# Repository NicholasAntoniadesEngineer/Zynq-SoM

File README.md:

# schgen

Generates the Zynq carrier and devkit boards from their C++ circuit definitions:
checked schematics, a placed board, design rules, manufacturing files and renders.
Routing is not done yet.

## Build

```sh
./build
```

Compiles the tool and runs the test suite (about 17 minutes). `./build --no-tests`
only compiles. Needs CMake, Ninja, ccache, a C++17 compiler, KiCad 10 and the
libraries listed in [native/ci/README.md](native/ci/README.md).

## Run

```sh
./run
```

Builds every board listed in `schgen.json` into `out/<board>/`. To build one board,
name it: `./run carrier`. A run ends with `BOARD: PASS` or `BOARD: FAIL`.

## Settings

Every setting lives in [`schgen.json`](schgen.json). Edit the file and run again;
nothing needs recompiling. A misspelt or unknown key stops the run with an error.

| Key | Default | Meaning |
|---|---|---|
| `boards` | `["carrier", "devkit_mini"]` | Boards to build, each a folder in this repository |
| `output` | `"out"` | Folder that receives one sub-folder per board |
| `squeeze` | `true` | Compact the placed board to the smallest outline that passes every rule |
| `arrange` | `true` | Before squeezing, move clusters of parts off sides of the module so those sides can close up; needs `squeeze` |
| `construct` | `false` | Before repair and squeezing, take every part that belongs to an owner off the board and seat it again by the layout rules; needs `squeeze` |
| `plan` | `true` | After the start is repaired, lift every group of tied parts that is free to move and seat it again, sheet by sheet, nearest the pins it connects to, with power and fast nets counted more heavily; then offer each group a nearer place. Every layout rule is checked on each seat. `reports/board_plan.txt` lists the wiring between sheets and how compact each sheet is; needs `squeeze` |
| `renders` | `true` | Produce the 3D and per-sheet images |
| `labels` | `false` | After the layout is final, seat each part's reference label beside it on its own face and draw the function labels. Parts never move for a label; one with no free seat is hidden and listed in `reports/label_seats.txt` |
| `timing` | `true` | Print how long each stage took |
| `plane_net` | `"GND"` | Net of the reference planes |
| `audit_projections` | `2` | Source audits run side by side (1 or 2) |
| `stackup` | `JLC06161H-3313` per board | Layer build-up, by name from the catalogue below |
| `density` | `10` per board | Layout density from 1 (sparse) to 10 (dense). 10 lets courtyards touch; each level below it adds 0.25 mm between courtyards on the same face, so 5 adds 1.25 mm and 1 adds 2.25 mm. No other rule is relaxed. Parts that a rule keeps together (a decoupling capacitor and its pin, a regulator and its loop, parts on one thermal area) keep no added gap between them; the gap opens between such clusters and around parts tied to nothing. One subsystem can state its own level with `"density": N` on its row under `sheets` in the board's `board.json`. Needs `squeeze` below 10. `reports/layout_density.txt` states the levels, the gaps, the table with its sources and every pair another rule limited |
| `overmold_parts` | `["HDMI-019S"]` on the carrier | Connectors whose cable overmould needs side clearance |
| `fabrication` | per board: `fabricator`, `copper`, `finish`, `assembly_service`, `build_count` | Which fabricator profile (`fabricators/<name>.json`) judges the board and orders it; see [docs/FABRICATION.md](docs/FABRICATION.md) |
| `study` | four builds, one per layer count | Optional: `stackups` lists the builds `study layers` compares |

## Layer build-ups

[`native/stackups.json`](native/stackups.json) lists the fabricator's standard
4, 6, 8 and 10-layer builds. To try another, put its name under `stackup` and run
again. The placed layout carries over between any two builds that have a ground
plane under both faces. To add a build, add an entry to that file.

To compare builds side by side, run `native/bin/schgen study layers` (optionally
`devkit_mini --stackups JLC06161H-3313,JLC08161H-3313`). Each build goes to
`out/study/<build>/<board>/` and the comparison to `out/study/layers_<board>.txt`
and `.json`. A build that fails a gate is recorded in its column; the rest still run.

## Where things are

| Folder | Holds |
|---|---|
| `carrier/`, `devkit_mini/` | Each board's design data and generated outputs |
| `subsystems/`, `parts/` | Shared circuit blocks and part data |
| `native/` | The tool's source and tests |
| `docs/` | Background; start with [docs/OVERVIEW.md](docs/OVERVIEW.md) |

`native/bin/schgen tools` lists the individual commands used for diagnosis.

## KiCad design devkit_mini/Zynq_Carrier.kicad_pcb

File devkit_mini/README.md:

<!-- schgen:gallery -->
<!-- GENERATED by `schgen gallery` — edits between these markers are overwritten -->
## Generated 3D board views

The placed board rendered from 8 angles by `schgen board` (kicad-cli, the real component 3D models) — regenerated and committed every build, just like the sheets below.

|   |   |   |   |
|---|---|---|---|
| <br>**Perspective (front)** | <br>**Perspective (rear)** | <br>**Top** | <br>**Bottom** |
| <br>**Front edge** | <br>**Back edge** | <br>**Left edge** | <br>**Right edge** |

## Ratsnest views

Placed-board airwires, regenerated by `schgen board`: blue/orange = the subsystem's parts (top/bottom side), steel = SoM, green = intra-subsystem, red = to the SoM. `wired` = in `placement.wired_sheets`.

|   |   |
|---|---|
| <br>**Board (top)** | <br>**Board (bottom)** |
| <br>**SoM region** |   |

|   |   |   |   |
|---|---|---|---|
| <br>**debug_boot** | <br>**mechanical** | <br>**pd_input** | <br>**power** |
| <br>**power_mon** | <br>**power_som** | <br>**uart_bridge** | <br>**usb_uart_connector** |

## Generated schematics

Block diagram and all 12 devkit_mini sheets, regenerated by `schgen board` —
every PNG below passed the netlist, ERC and visual gates.

|   |   |   |
|---|---|---|
| <br>**debug_boot** | <br>**mechanical** | <br>**pd_input** |
| <br>**power** | <br>**power_mon** | <br>**power_som** |
| <br>**som_decoupling** | <br>**som_j1** | <br>**som_j2** |
| <br>**som_j3** | <br>**uart_bridge** | <br>**usb_uart_connector** |

| sheet | description |
|---|---|
| [debug_boot](renders/debug_boot.png) | JTAG + SWD headers, boot-request DIP, reset |
| [mechanical](renders/mechanical.png) | Mechanical: M3 mounts + chassis-GND bond (fiducials are PCB-only, emitted by the placer) |
| [pd_input](renders/pd_input.png) | Power inlet: USB-C PD 20V/3A + TPS26631 eFuse |
| [power](renders/power.png) | Power: +VIN->+5V->+3V3 bucks + +1V8 LDO, PG LEDs |
| [power_mon](renders/power_mon.png) | Rail telemetry: 2x INA3221 + shunts (I2C 0x40/41) |
| [power_som](renders/power_som.png) | Power: +VIN -> +5V_SOM always-on buck |
| [som_decoupling](renders/som_decoupling.png) | SoM power-entry decoupling under the DF40 mezzanine |
| [som_j1](renders/som_j1.png) | SoM J1: power / USB / STM32 / JTAG / SDIO / ETH MDI |
| [som_j2](renders/som_j2.png) | SoM J2: FPGA bank 13/33 IO + VCCO rails |
| [som_j3](renders/som_j3.png) | SoM J3: FPGA bank 33/34/35 IO + VCCO rails |
| [uart_bridge](renders/uart_bridge.png) | UART bridge: CP2102N USB-UART |
| [usb_uart_connector](renders/usb_uart_connector.png) | USB-C UFP console port -> CP2102N |
<!-- /schgen:gallery -->

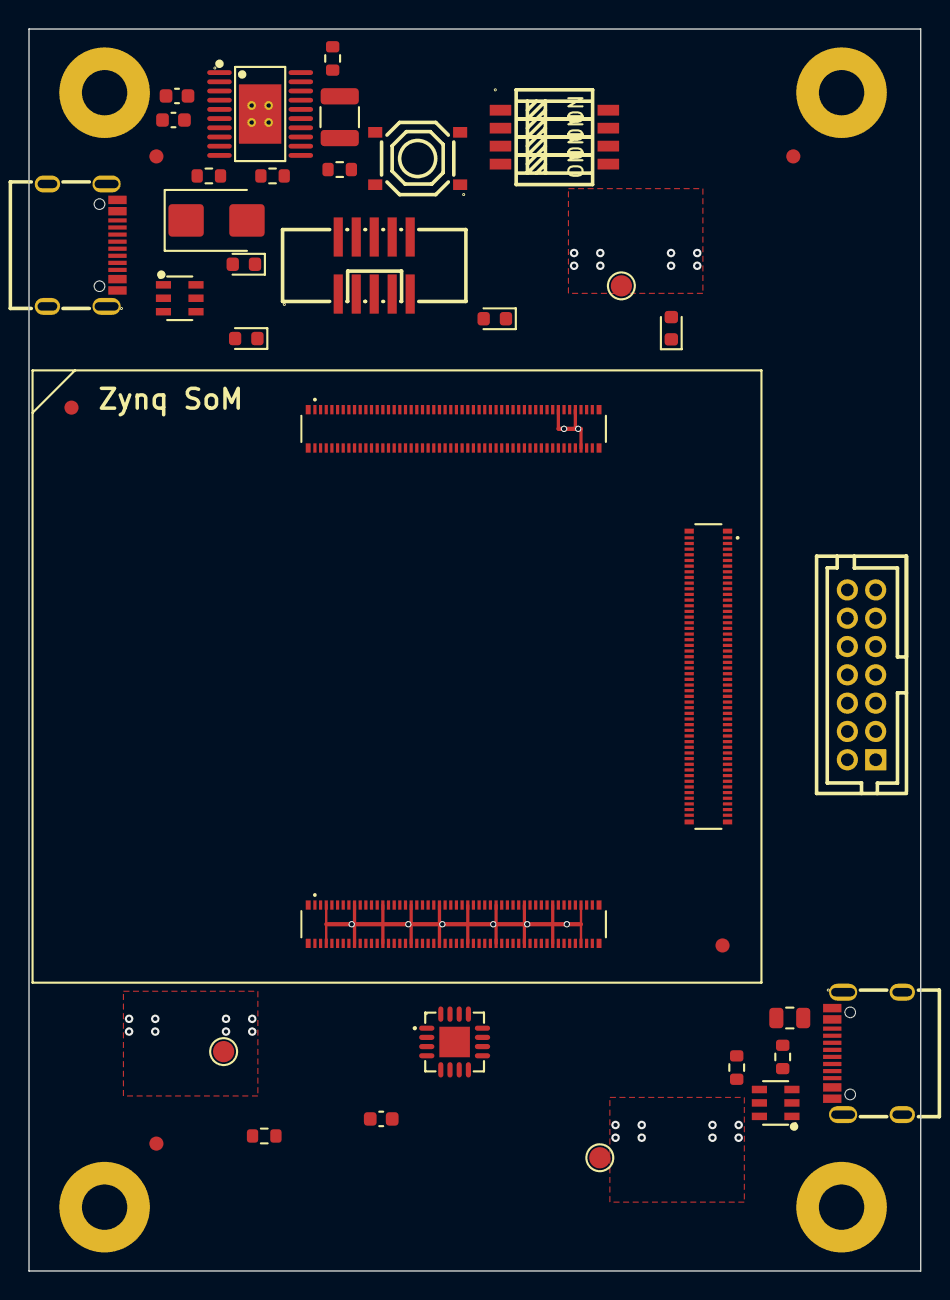
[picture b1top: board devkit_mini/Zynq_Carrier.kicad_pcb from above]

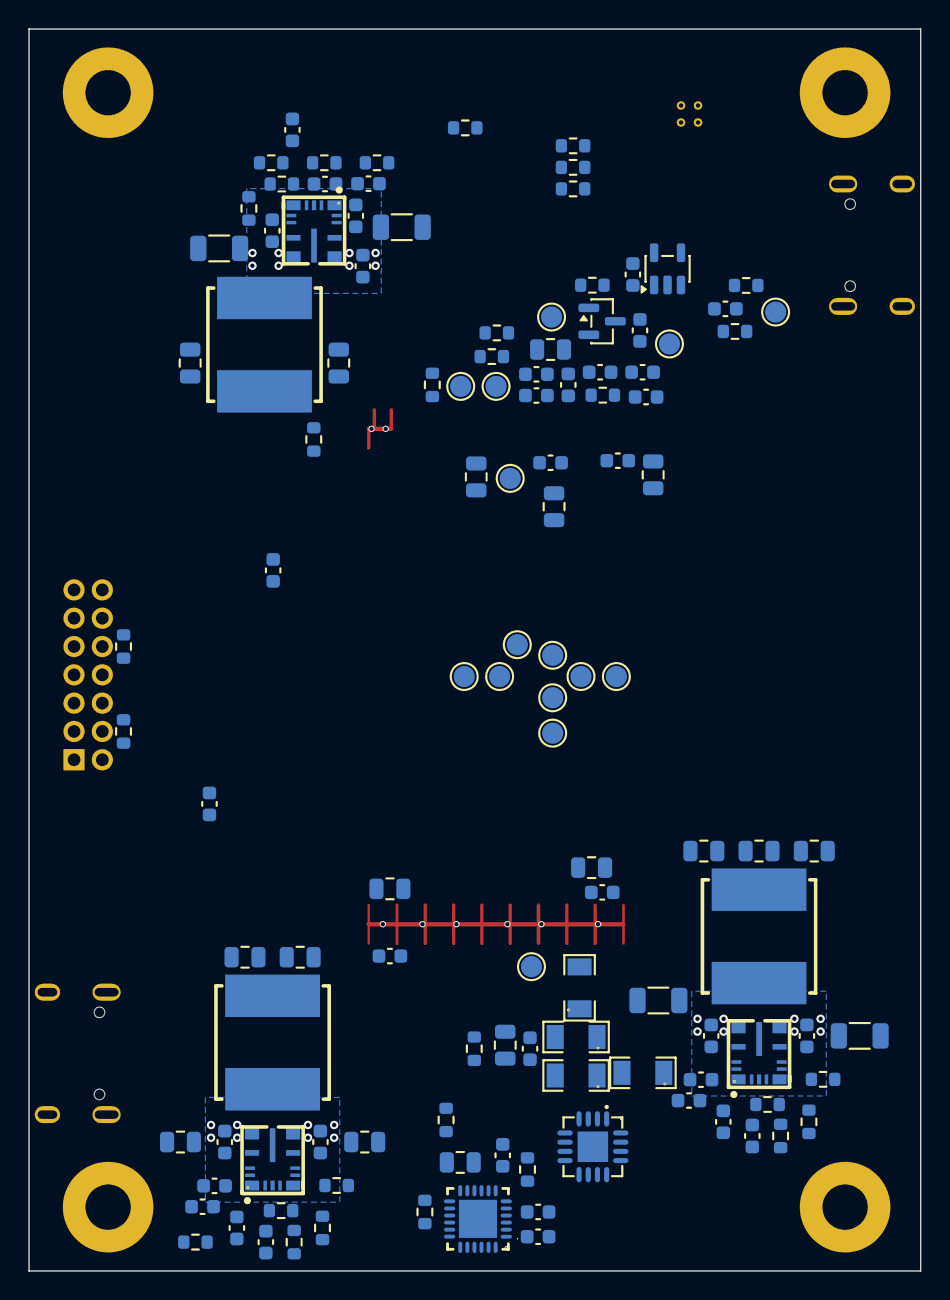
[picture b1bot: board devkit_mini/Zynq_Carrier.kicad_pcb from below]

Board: 6 copper layers, 63.0 x 87.8 mm, 161 parts (119 on the bottom side), 84 nets.

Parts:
C3001, C3004, C4001, C4004, C4007, C4009, C4025, C4029, C5001, C5002, C6014, C6017, C6025, C7003, C7004, C7005, C7006, C7009, C7010, C7011, C7012, C7015, C7016, C7017, C7018, C11001, C11003, C11004: 100n; C_0603_1608Metric
C3002: 10u; C_1210_3225Metric
C3003: 47n; C_0603_1608Metric
C4002, C4003, C6015, C6016: 10u; C_1206_3216Metric
C4005, C4006, C4008, C4010, C4011, C4026, C4030, C6018, C6019, C7001, C7002, C7007, C7008, C7013, C7014: 22u; C_0805_2012Metric
C4012, C4013, C4024, C4028, C4031, C4032, C6022, C6023: 1u; C_0603_1608Metric
C4023, C4027, C6021: 22p; C_0603_1608Metric
C5003, C11002, C12001: 10u; C_0805_2012Metric
D3001: SMBJ22A; D_SMB
D4001, D4002, D4003, D6004: red; LED_0603_1608Metric
FID1, FID2, FID3, FID4, FID5: Fiducial; Fiducial_1mm_Mask2mm
H2001, H2002, H2003, H2004: MountingHole_M3; MountingHole_3.2mm_M3_Pad
J1001: 878311420
J1002: HX_JN1.27-2x5; HX_JN1.27-2x5_TP_H4.9
J3001, J12001: TYPE-C-31-M-12
J8001, J9002, J10003: DF40C-100DP-0.4V(51); HRS_DF40C-100DP-0.4V_51_
L4001, L4002, L6003: 10uH; SWPA8040S100MT
Q4001: AO3400A; SOT-23
R1001, R1002, R1007, R1008: 4k7; R_0603_1608Metric
R1003: 100R; R_0603_1608Metric
R1004, R1005, R1006, R4002, R4005, R5001: 10k; R_0603_1608Metric
R3003, R3006, R4008: 100k; R_0603_1608Metric
R3004: 5.49k; R_0603_1608Metric
R3005, R12001, R12002: 5.1k; R_0603_1608Metric
R4001: 40.2k; R_0603_1608Metric
R4003, R4007, R4012, R4015, R6016, R6019, R11001: 1k; R_0603_1608Metric
R4004: 23.2k; R_0603_1608Metric
R4006, R4009: 330R; R_0603_1608Metric
R4010, R4014, R6018: 22k; R_0603_1608Metric
R4011, R4013, R6017: 10R; R_0603_1608Metric
R6014, R11003: 47k5; R_0603_1608Metric
R6015: 13k; R_0603_1608Metric
R11002: 22k1; R_0603_1608Metric
RS5001, RS5002, RS5003: 10mR; RLM12FTCMR010
RS5004: 20mR; RLM12FTCMR020
SW1001: DIP-4; DSHP04TSGER
SW1002: RESET; TS-1187A-B-A-B
TP1001: SDIO_CLK; TestPoint_Pad_D1.5mm
TP1002: SDIO_CMD; TestPoint_Pad_D1.5mm
TP1003: VBUS_OUT_EN; TestPoint_Pad_D1.5mm
TP3001: +VBUS_IN; TestPoint_Pad_D1.5mm
TP3002: +VIN; TestPoint_Pad_D1.5mm
TP4001: +5V; TestPoint_Pad_D1.5mm
TP4002: +3V3; TestPoint_Pad_D1.5mm
TP4003: +1V8; TestPoint_Pad_D1.5mm
TP4004: GND; TestPoint_Pad_D1.5mm
TP4005: EN_5V0; TestPoint_Pad_D1.5mm
TP4006: EN_3V3; TestPoint_Pad_D1.5mm
TP4007: EN_1V8; TestPoint_Pad_D1.5mm
TP5001: +3V3_SC; TestPoint_Pad_D1.5mm
TP5002: STM32_I2C2_SCL; TestPoint_Pad_D1.5mm
TP5003: STM32_I2C2_SDA; TestPoint_Pad_D1.5mm
TP6001: +5V_SOM; TestPoint_Pad_D1.5mm
TP11001: ZYNQ_PS_UART0_TXD; TestPoint_Pad_D1.5mm
TP11002: ZYNQ_PS_UART0_RXD; TestPoint_Pad_D1.5mm
U3001: TPS26631PWPR
U3002, U12001: USBLC6-2SC6
U4001, U4002, U6004: LM61460AANRJRR
U4003: AP2112K-1.8; SOT-23-5
U5001, U5002: INA3221AIRGVR
U11001: CP2102N-A02; CP2102N-A02-GQFN24R

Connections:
+1V8: R4007.1, RS5004.2, TP4003.1, U5002.11
+1V8_REG: C4013.1, RS5004.1, U4003.5, U5002.12
+3V3: C4012.1, C7007.1, C7008.1, C7009.1, C7010.1, C7011.1, C7012.1, C11001.1, C11002.1, C11003.1, C11004.1, D4003.2, J1001.2, J9002.1, J9002.2, J9002.3, J9002.98, J9002.99, J9002.100, J10003.1, J10003.2, J10003.4, J10003.97, J10003.99, R1001.1, R1002.1, R11001.1, RS5003.2, TP4002.1, U4003.1, U5001.1, U11001.5, U11001.6, U11001.7
+3V3_REG: C4010.1, C4011.1, C4023.1, D4002.2, L4002.2, R4004.1, R4013.1, RS5003.1, U5001.2
+3V3_SC: C3004.1, C5001.1, C5002.1, C5003.1, C7013.1, C7014.1, C7015.1, C7016.1, C7017.1, C7018.1, J1002.1, J8001.37, R1003.1, R1004.1, R1005.1, R1006.1, R1007.1, R1008.1, R3006.1, R5001.1, TP5001.1, U3002.5, U5001.4, U5001.16, U5002.4, U5002.5, U5002.16
+5V: C4007.1, C4008.1, C4029.1, C4030.1, RS5002.2, TP4001.1, U4002.8, U4002.12, U5001.14
+5V_REG: C4005.1, C4006.1, C4026.1, C4027.1, D4001.2, L4001.2, R4001.1, R4011.1, RS5002.1, U5001.15
+5V_SOM: C6018.1, C6019.1, C6021.1, C7001.1, C7002.1, C7003.1, C7004.1, C7005.1, C7006.1, D6004.2, J8001.1, J8001.2, J8001.3, J8001.4, J8001.5, J8001.6, J8001.7, J8001.8, J8001.9, J8001.10, J8001.11, J8001.12, J8001.13, J8001.14, L6003.2, R6014.1, R6017.1, TP6001.1
+VBUS_IN: C3001.1, D3001.1, J3001.A4B9, J3001.B4A9, R3003.1, TP3001.1, U3001.1, U3001.2, U3001.3, U3001.6, U3001.7
+VIN: C3002.1, RS5001.1, TP3002.1, U3001.18, U3001.19, U3001.20, U5001.12
+VIN_SYS: C4001.1, C4002.1, C4003.1, C4025.1, C6014.1, C6015.1, C6016.1, C6025.1, RS5001.2, U4001.8, U4001.12, U5001.11, U6004.7, U6004.8, U6004.12
/pd_input/PD_USB_DN_CONN: J3001.A7, J3001.B7, U3002.3
/pd_input/PD_USB_DP_CONN: J3001.A6, J3001.B6, U3002.1
/power/BIAS_3V3: C4032.1, R4013.2, U4002.1
/power/BIAS_5V0: C4028.1, R4011.2, U4001.1
/power/RT_3V3: R4014.1, U4002.6
/power/RT_5V0: R4010.1, U4001.6
/power_som/BIAS_5V_SOM: C6023.1, R6017.2, U6004.1
/power_som/RT_5V_SOM: R6018.1, U6004.6
/uart_bridge/CP2102N_VBUS_SNS: R11002.2, R11003.1, U11001.8
/usb_uart_connector/USB_UART_DM_CONN: J12001.A7, J12001.B7, U12001.3
/usb_uart_connector/USB_UART_DP_CONN: J12001.A6, J12001.B6, U12001.1
CHASSIS_GND: H2001.1, H2002.1, H2003.1, H2004.1, J3001.1, J3001.2, J3001.3, J3001.4, J12001.1, J12001.2, J12001.3, J12001.4
EN_1V8: TP4007.1, U4003.3
EN_3V3: TP4006.1, U4002.7
EN_5V0: TP4005.1, U4001.7
GND: C3001.2, C3002.2, C3003.2, C3004.2, C4001.2, C4002.2, C4003.2, C4005.2, C4006.2, C4007.2, C4008.2, C4010.2, C4011.2, C4012.2, C4013.2, C4024.2, C4025.2, C4026.2, C4028.2, C4029.2, C4030.2, C4031.2, C4032.2, C5001.2, C5002.2, C5003.2, C6014.2, C6015.2, C6016.2, C6018.2, C6019.2, C6022.2, C6023.2, C6025.2, C7001.2, C7002.2, C7003.2, C7004.2, C7005.2, C7006.2, C7007.2, C7008.2, C7009.2, C7010.2, C7011.2, C7012.2, C7013.2, C7014.2, C7015.2, C7016.2, C7017.2, C7018.2, C11001.2, C11002.2, C11003.2, C11004.2, C12001.2, D3001.2, J1001.1, J1001.3, J1001.5, J1001.7, J1001.9, J1001.11, J1001.13, J1002.3, J1002.5, J1002.9, J3001.A1B12, J3001.B1A12, J8001.15, J8001.16, J8001.17, J8001.18, J8001.23, J8001.28, J8001.34, J8001.39, J8001.44, J8001.51, J8001.62, J8001.63, J8001.72, J8001.75, J8001.81, J8001.82, J8001.87, J8001.93, J8001.96, J8001.99, J9002.4, J9002.5, J9002.6, J9002.15, J9002.16, J9002.25, J9002.26, J9002.35, J9002.36, J9002.45, J9002.46, J9002.55, J9002.56, J9002.65, J9002.66, J9002.75, J9002.76, J9002.85, J9002.86, J9002.95, J9002.96, J9002.97, J10003.3, J10003.6, J10003.12, J10003.13, J10003.18, J10003.23, J10003.28, J10003.33, J10003.38, J10003.43, J10003.48, J10003.53, J10003.58, J10003.63, J10003.68, J10003.73, J10003.80, J10003.83, J10003.90, J10003.95, J10003.100, J12001.A1B12, J12001.B1A12, Q4001.2, R3004.2, R3005.2, R4002.2, R4003.2, R4005.2, R4006.2, R4008.2, R4010.2, R4014.2, R6015.2, R6016.2, R6018.2, R11003.2, R12001.2, R12002.2, SW1001.5, SW1001.6, SW1001.7, SW1002.3, SW1002.4, TP4004.1, U3001.9, U3001.12, U3001.16, U3001.21, U3002.2, U4001.3, U4001.9, U4001.11, U4002.3, U4002.9, U4002.11, U4003.2, U5001.3, U5001.5, U5001.17, U5002.1, U5002.2, U5002.3, U5002.14, U5002.15, U5002.17, U6004.3, U6004.9, U6004.11, U11001.2, U11001.25, U12001.2
unnamed: C4023.2, R4015.1
unnamed: C4027.2, R4012.1
unnamed: C6021.2, R6019.1
unnamed: D4001.1, R4003.1
unnamed: D4002.1, R4006.1
unnamed: D4003.1, R4009.1
unnamed: D6004.1, R6016.1
unnamed: J12001.A5, R12001.1
unnamed: J12001.B5, R12002.1
unnamed: Q4001.3, R4009.2
unnamed: Q4001.1, R4007.2, R4008.1
unnamed: R1003.2, SW1001.8
unnamed: R1006.2, SW1001.4
unnamed: R3005.1, U3001.11
unnamed: R3003.2, R3004.1, U3001.8
unnamed: C3003.1, U3001.10
unnamed: C4004.1, U4001.13, U4001.14
unnamed: R4001.2, R4002.1, R4012.2, U4001.4
unnamed: C4004.2, L4001.1, U4001.10
unnamed: C4024.1, U4001.2
unnamed: C4009.1, U4002.13, U4002.14
unnamed: R4004.2, R4005.1, R4015.2, U4002.4
unnamed: C4009.2, L4002.1, U4002.10
unnamed: C4031.1, U4002.2
unnamed: C6017.1, U6004.13, U6004.14
unnamed: R6014.2, R6015.1, R6019.2, U6004.4
unnamed: C6017.2, L6003.1, U6004.10
unnamed: C6022.1, U6004.2
unnamed: R11001.2, U11001.9
PD_FLT_N: R3006.2, U3001.15
PMON_ALERT_N: R5001.2, U5001.9, U5002.9
SDIO_CLK: J8001.67, TP1001.1
SDIO_CMD: J8001.69, TP1002.1
STM32_BOOT0: J8001.57, SW1001.1
STM32_GPIO5: J1002.4, J8001.53
STM32_GPIO6: J1002.2, J8001.45
STM32_GPIO7: J8001.59, R1004.2, SW1001.2
STM32_GPIO8: J8001.54, R1005.2, SW1001.3
STM32_I2C2_SCL: J8001.55, R1007.2, TP5002.1, U5001.6, U5002.6
STM32_I2C2_SDA: J8001.49, R1008.2, TP5003.1, U5001.7, U5002.7
STM32_NRST: J1002.10, J8001.47, SW1002.1, SW1002.2
STM32_USB_CC1: J3001.A5, J8001.29
STM32_USB_CC2: J3001.B5, J8001.31
STM32_USB_D_N: J8001.21, U3002.4
STM32_USB_D_P: J8001.19, U3002.6
USB_UART_DM: U11001.4, U12001.4
USB_UART_DP: U11001.3, U12001.6
USB_UART_VBUS: C12001.1, J12001.A4B9, J12001.B4A9, R11002.1, U12001.5
VBUS_OUT_EN: J8001.38, TP1003.1
ZYNQ_PS_UART0_CTS_N: J9002.11, U11001.19
ZYNQ_PS_UART0_RTS_N: J9002.8, U11001.18
ZYNQ_PS_UART0_RXD: J8001.42, TP11002.1, U11001.21
ZYNQ_PS_UART0_TXD: J8001.48, TP11001.1, U11001.20
ZYNQ_TCK: J1001.6, J8001.64
ZYNQ_TDI: J1001.10, J8001.70, R1002.2
ZYNQ_TDO: J1001.8, J8001.68
ZYNQ_TMS: J1001.4, J8001.66, R1001.2

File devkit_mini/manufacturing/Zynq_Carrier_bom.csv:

Comment,Designator,Footprint,JLCPCB Part #
100R,R1003,Resistor_SMD:R_0603_1608Metric,C22775
100k,"R3003,R3006,R4008",Resistor_SMD:R_0603_1608Metric,C25803
100n,"C3001,C3004,C4001,C4004,C4007,C4009,C4025,C4029,C5001,C5002,C6014,C6017,C6025,C7003,C7004,C7005,C7006,C7009,C7010,C7011,C7012,C7015,C7016,C7017,C7018,C11001,C11003,C11004",Capacitor_SMD:C_0603_1608Metric,C14663
10R,"R4011,R4013,R6017",Resistor_SMD:R_0603_1608Metric,C22859
10k,"R1004,R1005,R1006,R4002,R4005,R5001",Resistor_SMD:R_0603_1608Metric,C25804
10mR,"RS5001,RS5002,RS5003",RLM12FTCMR010:RLM12FTCMR010,C188070
10u,"C5003,C11002,C12001",Capacitor_SMD:C_0805_2012Metric,C15850
10u,"C4002,C4003,C6015,C6016",Capacitor_SMD:C_1206_3216Metric,C13585
10u,C3002,Capacitor_SMD:C_1210_3225Metric,C596319
10uH,"L4001,L4002,L6003",SWPA8040S100MT:SWPA8040S100MT,C37429
13k,R6015,Resistor_SMD:R_0603_1608Metric,C22797
1k,"R4003,R4007,R4012,R4015,R6016,R6019,R11001",Resistor_SMD:R_0603_1608Metric,C21190
1u,"C4012,C4013,C4024,C4028,C4031,C4032,C6022,C6023",Capacitor_SMD:C_0603_1608Metric,C15849
20mR,RS5004,RLM12FTCMR020:RLM12FTCMR020,C393094
22k,"R4010,R4014,R6018",Resistor_SMD:R_0603_1608Metric,C31850
22k1,R11002,Resistor_SMD:R_0603_1608Metric,C25961
22p,"C4023,C4027,C6021",Capacitor_SMD:C_0603_1608Metric,C1653
22u,"C4005,C4006,C4008,C4010,C4011,C4026,C4030,C6018,C6019,C7001,C7002,C7007,C7008,C7013,C7014",Capacitor_SMD:C_0805_2012Metric,C45783
23.2k,R4004,Resistor_SMD:R_0603_1608Metric,C23346
330R,"R4006,R4009",Resistor_SMD:R_0603_1608Metric,C23138
40.2k,R4001,Resistor_SMD:R_0603_1608Metric,C12447
47k5,"R6014,R11003",Resistor_SMD:R_0603_1608Metric,C23061
47n,C3003,Capacitor_SMD:C_0603_1608Metric,C1622
4k7,"R1001,R1002,R1007,R1008",Resistor_SMD:R_0603_1608Metric,C23162
5.1k,"R3005,R12001,R12002",Resistor_SMD:R_0603_1608Metric,C23186
5.49k,R3004,Resistor_SMD:R_0603_1608Metric,C188263
878311420,J1001,878311420:878311420,C240854
AO3400A,Q4001,Package_TO_SOT_SMD:SOT-23,C20917
AP2112K-1.8,U4003,Package_TO_SOT_SMD:SOT-23-5,C176944
CP2102N-A02,U11001,CP2102N-A02-GQFN24R:CP2102N-A02-GQFN24R,C969151
DF40C-100DP-0.4V(51),"J8001,J9002,J10003",Mylibrary:HRS_DF40C-100DP-0.4V_51_,C531031
DIP-4,SW1001,DSHP04TSGER:DSHP04TSGER,C3293144
HX_JN1.27-2x5,J1002,HX_JN1.27-2x5_TP_H4.9:HX_JN1.27-2x5_TP_H4.9,C42372555
INA3221AIRGVR,"U5001,U5002",INA3221AIRGVR:INA3221AIRGVR,C181255
LM61460AANRJRR,"U4001,U4002,U6004",LM61460AANRJRR:LM61460AANRJRR,C2864505
RESET,SW1002,TS-1187A-B-A-B:TS-1187A-B-A-B,C318884
SMBJ22A,D3001,Diode_SMD:D_SMB,C10214
TPS26631PWPR,U3001,TPS26631PWPR:TPS26631PWPR,C2866319
TYPE-C-31-M-12,"J3001,J12001",TYPE-C-31-M-12:TYPE-C-31-M-12,C165948
USBLC6-2SC6,"U3002,U12001",USBLC6-2SC6:USBLC6-2SC6,C7519
red,"D4001,D4002,D4003,D6004",LED_SMD:LED_0603_1608Metric,C2286

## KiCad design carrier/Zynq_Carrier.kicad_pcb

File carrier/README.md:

<!-- schgen:gallery -->
<!-- GENERATED by `schgen gallery` — edits between these markers are overwritten -->
## Generated 3D board views

The placed board rendered from 8 angles by `schgen board` (kicad-cli, the real component 3D models) — regenerated and committed every build, just like the sheets below.

|   |   |   |   |
|---|---|---|---|
| <br>**Perspective (front)** | <br>**Perspective (rear)** | <br>**Top** | <br>**Bottom** |
| <br>**Front edge** | <br>**Back edge** | <br>**Left edge** | <br>**Right edge** |

## Ratsnest views

Placed-board airwires, regenerated by `schgen board`: blue/orange = the subsystem's parts (top/bottom side), steel = SoM, green = intra-subsystem, red = to the SoM. `wired` = in `placement.wired_sheets`.

|   |   |
|---|---|
| <br>**Board (top)** | <br>**Board (bottom)** |
| <br>**SoM region** |   |

|   |   |   |   |
|---|---|---|---|
| <br>**board_aux** | <br>**board_qwiic** | <br>**board_services** | <br>**bringup_en** |
| <br>**bringup_en_modules** | <br>**bringup_modules** | <br>**bringup_rails** | <br>**camera** |
| <br>**debug_boot** | <br>**ethernet** | <br>**fmc** | <br>**hdmi_rx** |
| <br>**hdmi_rx_term** | <br>**hdmi_tx** | <br>**lcd** | <br>**mechanical** |
| <br>**microsd** | <br>**motor_pwm** | <br>**motor_sense** | <br>**pd_input** |
| <br>**pmod** | <br>**pmod_expansion** | <br>**power** | <br>**power_mon** |
| <br>**power_som** | <br>**rj45_connector** | <br>**uart_bridge** | <br>**usb_jtag** |
| <br>**usb_jtag_connector** | <br>**usb_pd** | <br>**usb_uart_connector** | <br>**usbc_otg** |
| <br>**user_io** |   |   |   |

## Generated schematics

Block diagram and all 37 carrier sheets, regenerated by `schgen board` —
every PNG below passed the netlist, ERC and visual gates.

|   |   |   |
|---|---|---|
| <br>**board_aux** | <br>**board_qwiic** | <br>**board_services** |
| <br>**bringup_en** | <br>**bringup_en_modules** | <br>**bringup_modules** |
| <br>**bringup_rails** | <br>**camera** | <br>**debug_boot** |
| <br>**ethernet** | <br>**fmc** | <br>**hdmi_rx** |
| <br>**hdmi_rx_term** | <br>**hdmi_tx** | <br>**lcd** |
| <br>**mechanical** | <br>**microsd** | <br>**motor_pwm** |
| <br>**motor_sense** | <br>**pd_input** | <br>**pmod** |
| <br>**pmod_expansion** | <br>**power** | <br>**power_mon** |
| <br>**power_som** | <br>**rj45_connector** | <br>**som_decoupling** |
| <br>**som_j1** | <br>**som_j2** | <br>**som_j3** |
| <br>**uart_bridge** | <br>**usb_jtag** | <br>**usb_jtag_connector** |
| <br>**usb_pd** | <br>**usb_uart_connector** | <br>**usbc_otg** |
| <br>**user_io** |   |   |

| sheet | description |
|---|---|
| [board_aux](renders/board_aux.png) | Board services: gated +3V3_AUX rail + PCA9306 I2C isolator |
| [board_qwiic](renders/board_qwiic.png) | QWIIC / STEMMA-QT expansion connector + USBLC6 ESD array |
| [board_services](renders/board_services.png) | Board services: ID-EEPROM, RTC, watchdog, QWIIC |
| [bringup_en](renders/bringup_en.png) | Bring-up EN cells: 3x SN74LVC1G08 rail DIP-AND-override |
| [bringup_en_modules](renders/bringup_en_modules.png) | Bring-up EN cells: 11x SN74LVC1G08 module DIP-AND-override |
| [bringup_modules](renders/bringup_modules.png) | Bring-up module gates: 10x SY6280 + status/user LEDs |
| [bringup_rails](renders/bringup_rails.png) | Bring-up controls: rail/module DIPs + TCA9535 + buttons |
| [camera](renders/camera.png) | RPi camera port: 2-lane MIPI CSI-2 (15P FFC) |
| [debug_boot](renders/debug_boot.png) | JTAG + SWD headers, boot-request DIP, reset |
| [ethernet](renders/ethernet.png) | Ethernet: HX5008NL magnetics + Bob-Smith |
| [fmc](renders/fmc.png) | SoM bank-35 IO breakout (2x20 2.54mm header, VADJ 2.5V) |
| [hdmi_rx](renders/hdmi_rx.png) | HDMI RX: HDMI-A sink + EDID EEPROM |
| [hdmi_rx_term](renders/hdmi_rx_term.png) | HDMI-RX TMDS sink termination (8x49.9R to AVCC=+3V3) |
| [hdmi_tx](renders/hdmi_tx.png) | HDMI TX: TPD12S016 + HDMI-A receptacle (source) |
| [lcd](renders/lcd.png) | 40-pin TTL RGB LCD + SY7201 backlight boost |
| [mechanical](renders/mechanical.png) | Mechanical: M3 mounts + chassis-GND bond (fiducials are PCB-only, emitted by the placer) |
| [microsd](renders/microsd.png) | microSD slot (1.8V SoM <-> 3.3V card, TXS02612) |
| [motor_pwm](renders/motor_pwm.png) | 8-ch PWM/ESC output buffer (5V, PL-isolating) |
| [motor_sense](renders/motor_sense.png) | ESC motor-rail telemetry: INA3221 + 10mR shunt (I2C 0x42) |
| [pd_input](renders/pd_input.png) | Power inlet: USB-C PD 20V/3A + TPS26631 eFuse |
| [pmod](renders/pmod.png) | 2x Pmod host ports (bank 13, 200R series, gated 3V3) |
| [pmod_expansion](renders/pmod_expansion.png) | Pmod expansion (2x6, bank 13, ESD, gated 3V3) |
| [power](renders/power.png) | Power: +VIN->+5V->+3V3 bucks + +1V8 LDO, PG LEDs |
| [power_mon](renders/power_mon.png) | Rail telemetry: 2x INA3221 + shunts (I2C 0x40/41) |
| [power_som](renders/power_som.png) | Power: +VIN -> +5V_SOM always-on buck |
| [rj45_connector](renders/rj45_connector.png) | RJ45 8P8C jack (plain, ext. magnetics) |
| [som_decoupling](renders/som_decoupling.png) | SoM power-entry decoupling under the DF40 mezzanine |
| [som_j1](renders/som_j1.png) | SoM J1: power / USB / STM32 / JTAG / SDIO / ETH MDI |
| [som_j2](renders/som_j2.png) | SoM J2: FPGA bank 13/33 IO + VCCO rails |
| [som_j3](renders/som_j3.png) | SoM J3: FPGA bank 33/34/35 IO + VCCO rails |
| [uart_bridge](renders/uart_bridge.png) | UART bridge: CP2102N USB-UART |
| [usb_jtag](renders/usb_jtag.png) | USB-JTAG/UART bridge: CH347T, isolated |
| [usb_jtag_connector](renders/usb_jtag_connector.png) | USB-C UFP debug port -> CH347T (protected) |
| [usb_pd](renders/usb_pd.png) | USB-PD: FUSB302B Type-C controller |
| [usb_uart_connector](renders/usb_uart_connector.png) | USB-C UFP console port -> CP2102N |
| [usbc_otg](renders/usbc_otg.png) | USB 2.0 HS OTG port (Type-C, host) |
| [user_io](renders/user_io.png) | User IO: 4 LEDs (gated rail) + 4 buttons, bank 13 |
<!-- /schgen:gallery -->

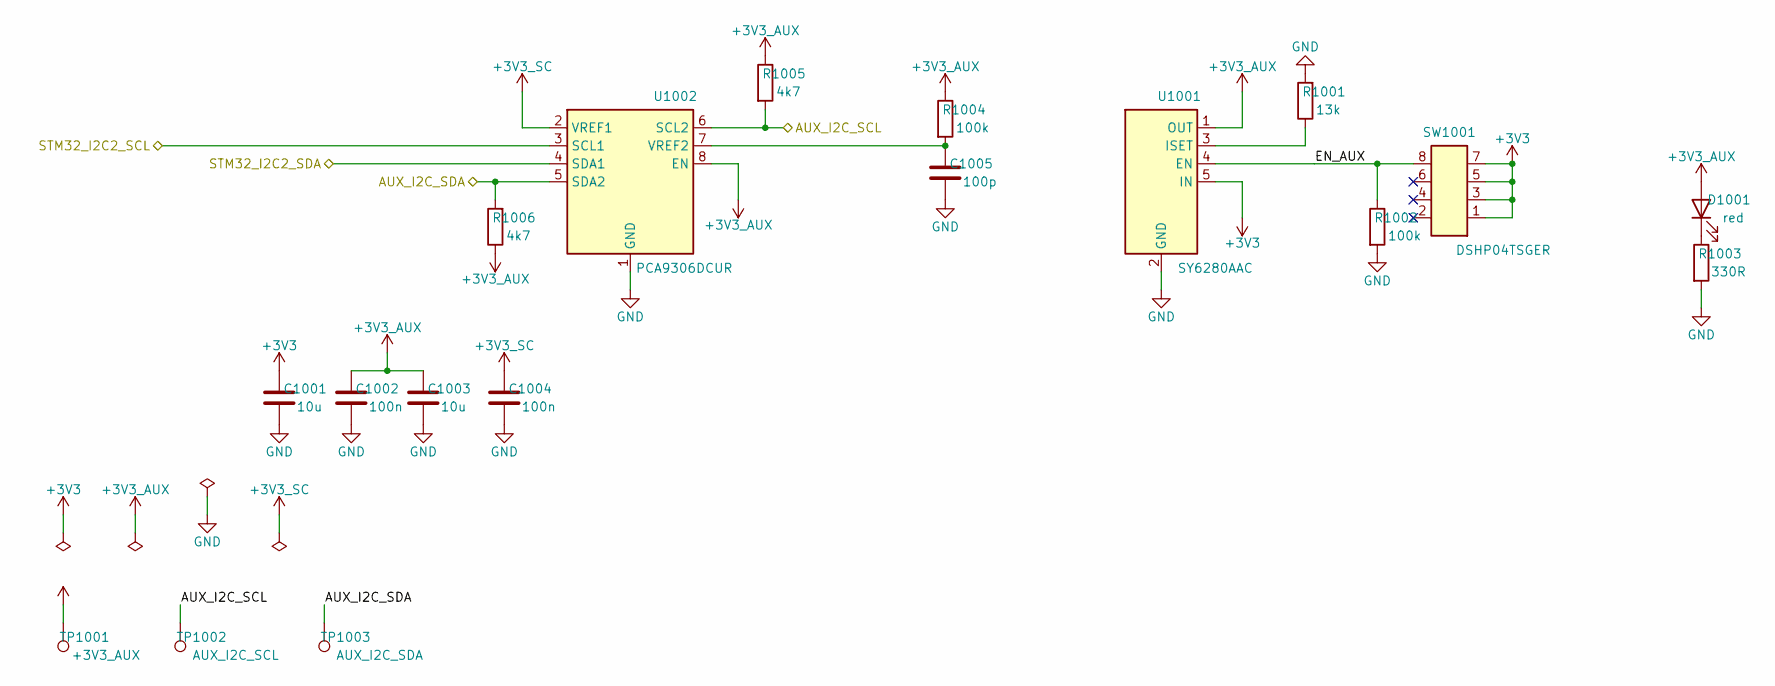
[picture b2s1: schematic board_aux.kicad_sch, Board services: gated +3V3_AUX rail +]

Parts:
C1001, C1003: 10u; C_0805_2012Metric; LCSC C15850
C1002, C1004: 100n; C_0603_1608Metric; LCSC C14663
C1005: 100p; C_0603_1608Metric; LCSC C14858
D1001: red; LED_0603_1608Metric; LCSC C2286
R1001: 13k; R_0603_1608Metric; LCSC C22797
R1002, R1004: 100k; R_0603_1608Metric; LCSC C25803
R1003: 330R; R_0603_1608Metric; LCSC C23138
R1005, R1006: 4k7; R_0603_1608Metric; LCSC C23162
SW1001: DSHP04TSGER; LCSC C3293144
TP1001: +3V3_AUX; TestPoint_Pad_D1.5mm
TP1002: AUX_I2C_SCL; TestPoint_Pad_D1.5mm
TP1003: AUX_I2C_SDA; TestPoint_Pad_D1.5mm
U1001: SY6280AAC; LCSC C55136
U1002: PCA9306DCUR; LCSC C33196

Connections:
+3V3: C1001.1, SW1001.1, SW1001.3, SW1001.5, SW1001.7, U1001.5 (IN); also elsewhere on the board
+3V3_AUX: C1002.1, C1003.1, D1001.2 (A), R1004.1, R1005.1, R1006.1, TP1001.1, U1001.1 (OUT), U1002.8 (EN); also elsewhere on the board
+3V3_SC: C1004.1, U1002.2 (VREF1); also elsewhere on the board
/board_aux/EN_AUX: R1002.1, SW1001.8, U1001.4 (EN)
AUX_I2C_SCL: R1005.2, TP1002.1, U1002.6 (SCL2); also elsewhere on the board
AUX_I2C_SDA: R1006.2, TP1003.1, U1002.5 (SDA2); also elsewhere on the board
GND: C1001.2, C1002.2, C1003.2, C1004.2, C1005.2, R1001.2, R1002.2, R1003.2, U1001.2 (GND), U1002.1 (GND); also elsewhere on the board
unnamed: D1001.1 (K), R1003.1
unnamed: R1001.1, U1001.3 (ISET)
unnamed: C1005.1, R1004.2, U1002.7 (VREF2)
STM32_I2C2_SCL: U1002.3 (SCL1); also elsewhere on the board
STM32_I2C2_SDA: U1002.4 (SDA1); also elsewhere on the board

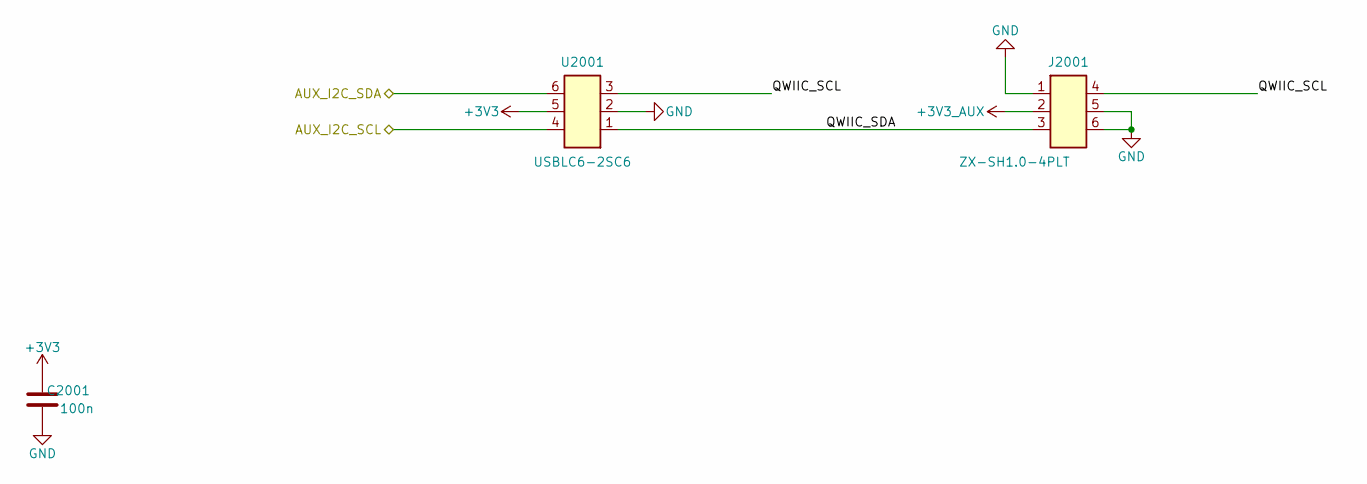
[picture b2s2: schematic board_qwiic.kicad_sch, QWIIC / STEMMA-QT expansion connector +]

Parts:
C2001: 100n; C_0603_1608Metric; LCSC C14663
J2001: ZX-SH1.0-4PLT; LCSC C7430453
U2001: USBLC6-2SC6; LCSC C7519

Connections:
+3V3: C2001.1, U2001.5; also elsewhere on the board
+3V3_AUX: J2001.2; also elsewhere on the board
/board_qwiic/QWIIC_SCL: J2001.4, U2001.3
/board_qwiic/QWIIC_SDA: J2001.3, U2001.1
AUX_I2C_SCL: U2001.4; also elsewhere on the board
AUX_I2C_SDA: U2001.6; also elsewhere on the board
GND: C2001.2, J2001.1, J2001.5, J2001.6, U2001.2; also elsewhere on the board

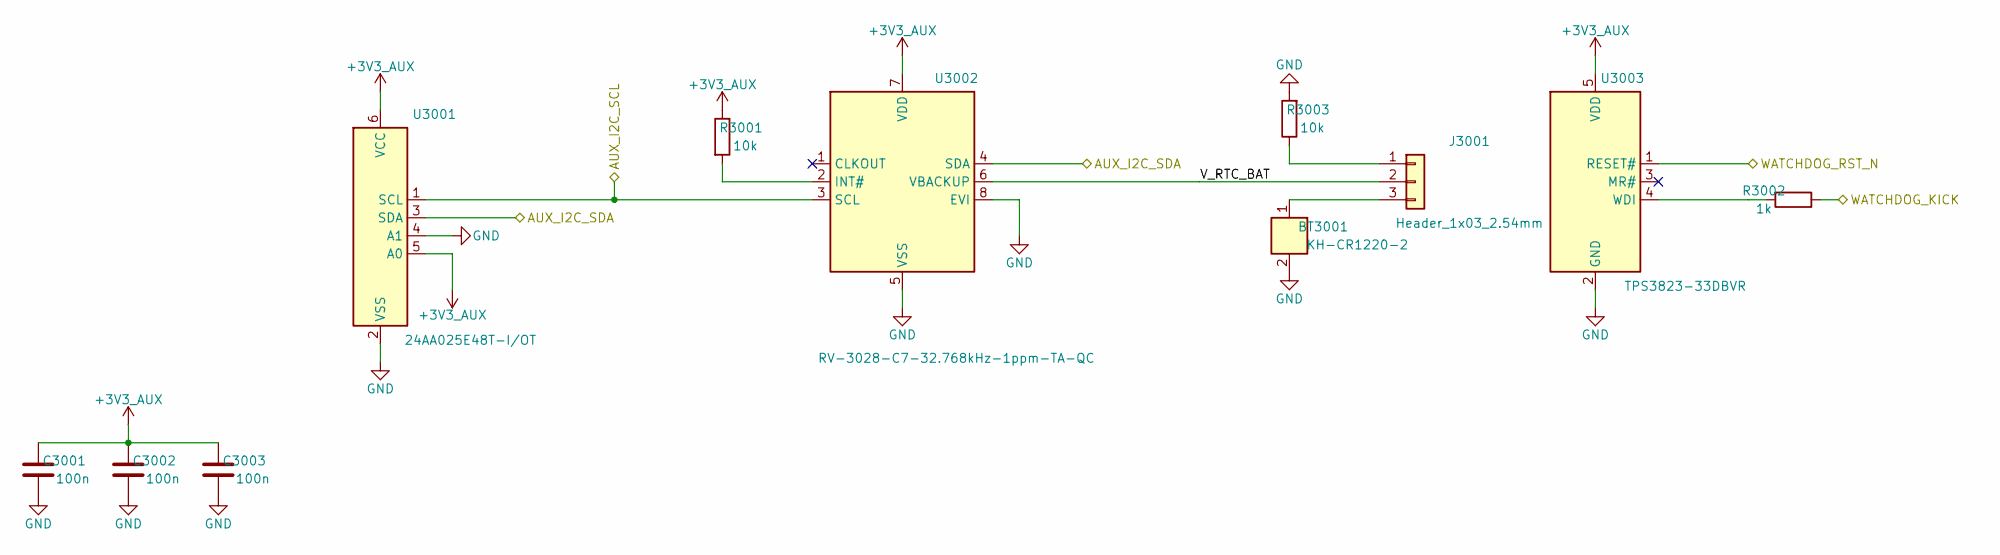
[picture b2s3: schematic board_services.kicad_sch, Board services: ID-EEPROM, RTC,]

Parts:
BT3001: KH-CR1220-2; LCSC C5365933
C3001, C3002, C3003: 100n; C_0603_1608Metric; LCSC C14663
J3001: Header_1x03_2.54mm; PinHeader_1x03_P2.54mm_Vertical; LCSC C49257
R3001, R3003: 10k; R_0603_1608Metric; LCSC C25804
R3002: 1k; R_0603_1608Metric; LCSC C21190
U3001: 24AA025E48T-I/OT; 24AA025E48T-I_OT; LCSC C129895
U3002: RV-3028-C7-32.768kHz-1ppm-TA-QC; LCSC C3019759
U3003: TPS3823-33DBVR; LCSC C7719

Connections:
+3V3_AUX: C3001.1, C3002.1, C3003.1, R3001.1, U3001.5 (A0), U3001.6 (VCC), U3002.7 (VDD), U3003.5 (VDD); also elsewhere on the board
/board_services/V_RTC_BAT: J3001.2, U3002.6 (VBACKUP)
AUX_I2C_SCL: U3001.1 (SCL), U3002.3 (SCL); also elsewhere on the board
AUX_I2C_SDA: U3001.3 (SDA), U3002.4 (SDA); also elsewhere on the board
GND: BT3001.2, C3001.2, C3002.2, C3003.2, R3003.2, U3001.2 (VSS), U3001.4 (A1), U3002.5 (VSS), U3002.8 (EVI), U3003.2 (GND); also elsewhere on the board
unnamed: J3001.1, R3003.1
unnamed: BT3001.1, J3001.3
unnamed: R3001.2, U3002.2 (INT#)
unnamed: R3002.2, U3003.4 (WDI)
WATCHDOG_KICK: R3002.1; also elsewhere on the board
WATCHDOG_RST_N: U3003.1 (RESET#); also elsewhere on the board

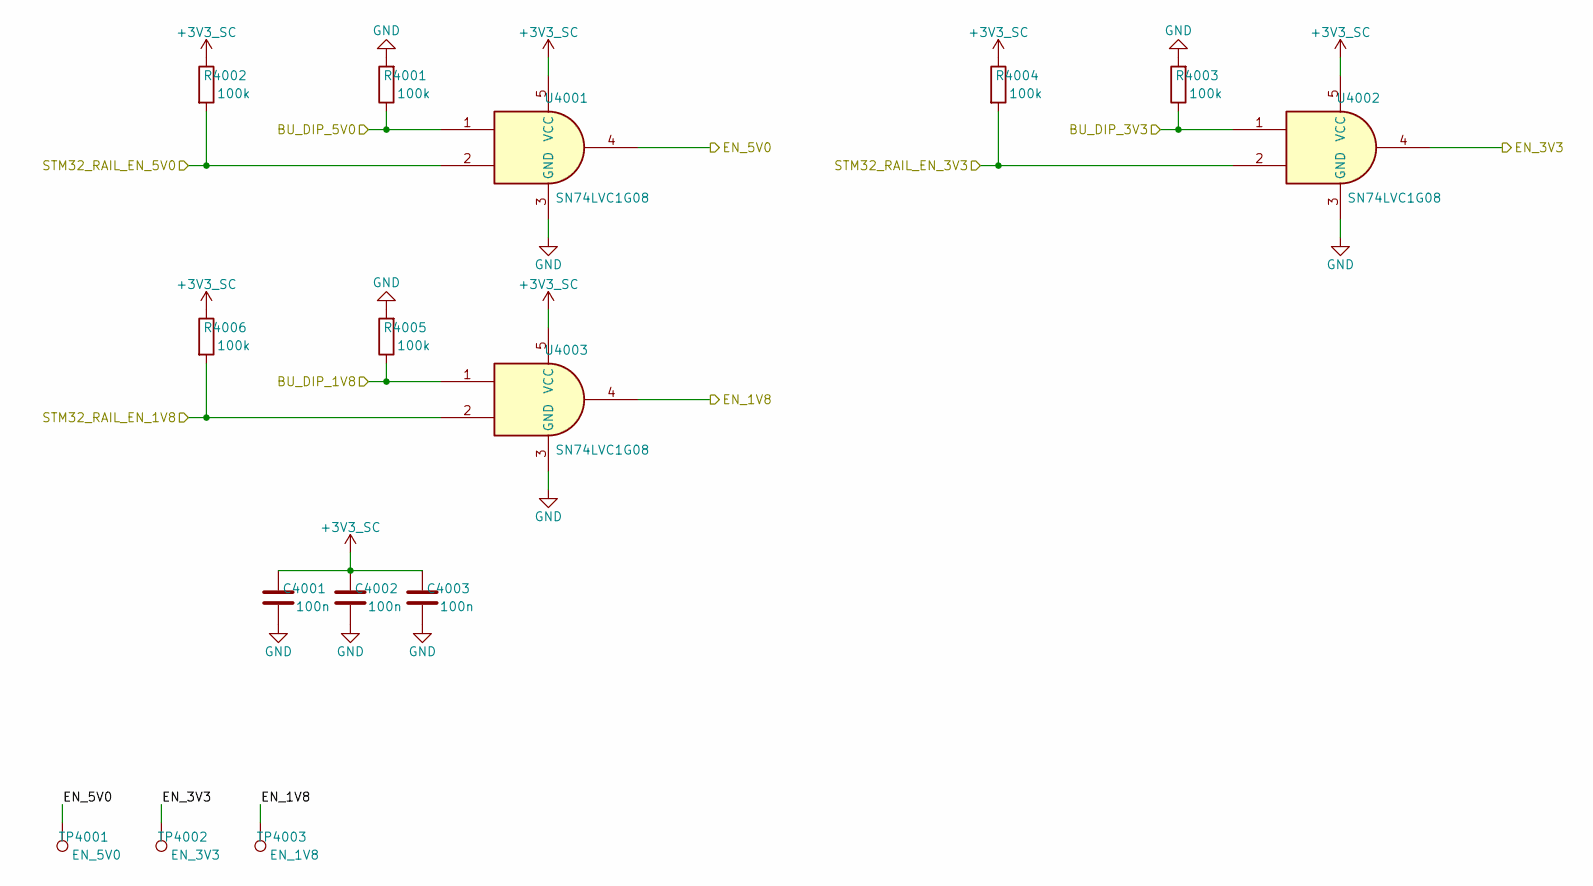
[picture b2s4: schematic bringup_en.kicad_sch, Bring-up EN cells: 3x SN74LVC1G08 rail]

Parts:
C4001, C4002, C4003: 100n; C_0603_1608Metric; LCSC C14663
R4001, R4002, R4003, R4004, R4005, R4006: 100k; R_0603_1608Metric; LCSC C25803
TP4001: EN_5V0; TestPoint_Pad_D1.5mm
TP4002: EN_3V3; TestPoint_Pad_D1.5mm
TP4003: EN_1V8; TestPoint_Pad_D1.5mm
U4001, U4002, U4003: SN74LVC1G08; SOT-23-5; LCSC C7666

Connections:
+3V3_SC: C4001.1, C4002.1, C4003.1, R4002.1, R4004.1, R4006.1, U4001.5 (VCC), U4002.5 (VCC), U4003.5 (VCC); also elsewhere on the board
BU_DIP_1V8: R4005.1, U4003.1; also elsewhere on the board
BU_DIP_3V3: R4003.1, U4002.1; also elsewhere on the board
BU_DIP_5V0: R4001.1, U4001.1; also elsewhere on the board
EN_1V8: TP4003.1, U4003.4; also elsewhere on the board
EN_3V3: TP4002.1, U4002.4; also elsewhere on the board
EN_5V0: TP4001.1, U4001.4; also elsewhere on the board
GND: C4001.2, C4002.2, C4003.2, R4001.2, R4003.2, R4005.2, U4001.3 (GND), U4002.3 (GND), U4003.3 (GND); also elsewhere on the board
STM32_RAIL_EN_1V8: R4006.2, U4003.2; also elsewhere on the board
STM32_RAIL_EN_3V3: R4004.2, U4002.2; also elsewhere on the board
STM32_RAIL_EN_5V0: R4002.2, U4001.2; also elsewhere on the board
